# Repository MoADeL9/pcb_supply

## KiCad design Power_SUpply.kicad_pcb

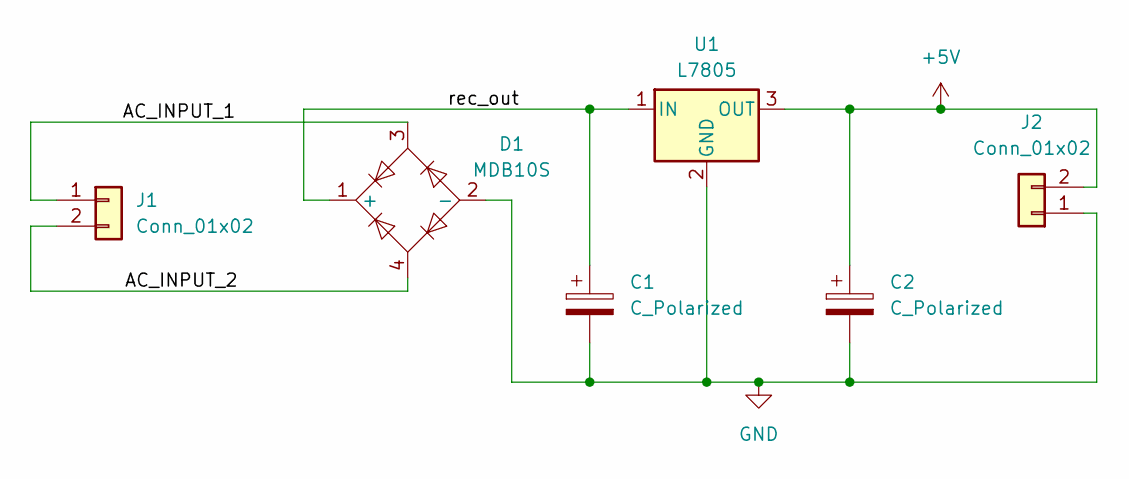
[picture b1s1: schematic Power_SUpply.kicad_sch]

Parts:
C1, C2: C_Polarized; CP_Radial_D5.0mm_P2.00mm
D1: MDB10S; TSSOP-4_4.4x5mm_P4mm
J1, J2: Conn_01x02; TerminalBlock_Phoenix_MKDS-1,5-2_1x02_P5.00mm_Horizontal
U1: L7805; TO-220-3_Vertical

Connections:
+5V: C2.1, J2.2, U1.3 (OUT)
/AC_INPUT_1: D1.3, J1.1
/AC_INPUT_2: D1.4, J1.2
/rec_out: C1.1, D1.1 (+), U1.1 (IN)
GND: C1.2, C2.2, D1.2 (-), J2.1, U1.2 (GND)

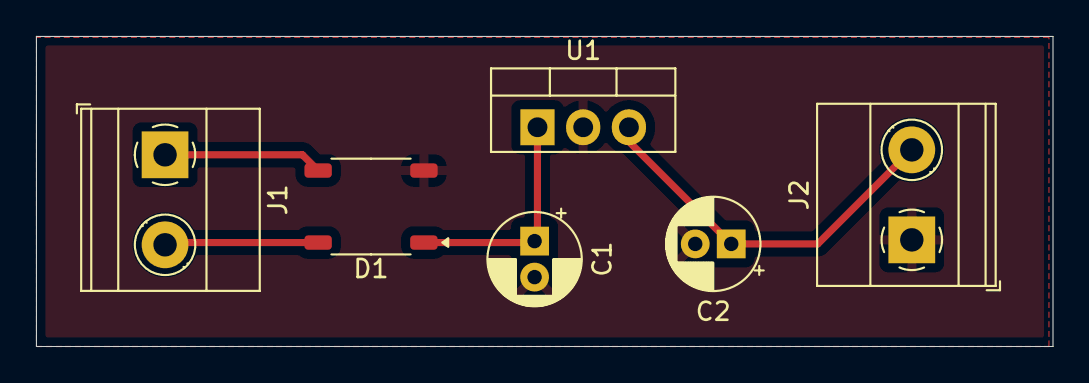
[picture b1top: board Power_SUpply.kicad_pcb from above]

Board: 2 copper layers, 56.5 x 17.2 mm, 6 parts (0 on the bottom side), 5 nets.

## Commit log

2025-05-17 edited schematic design
2025-05-17 third one
2025-05-17 changed the connector
2025-05-17 changed connector to screw terminal
